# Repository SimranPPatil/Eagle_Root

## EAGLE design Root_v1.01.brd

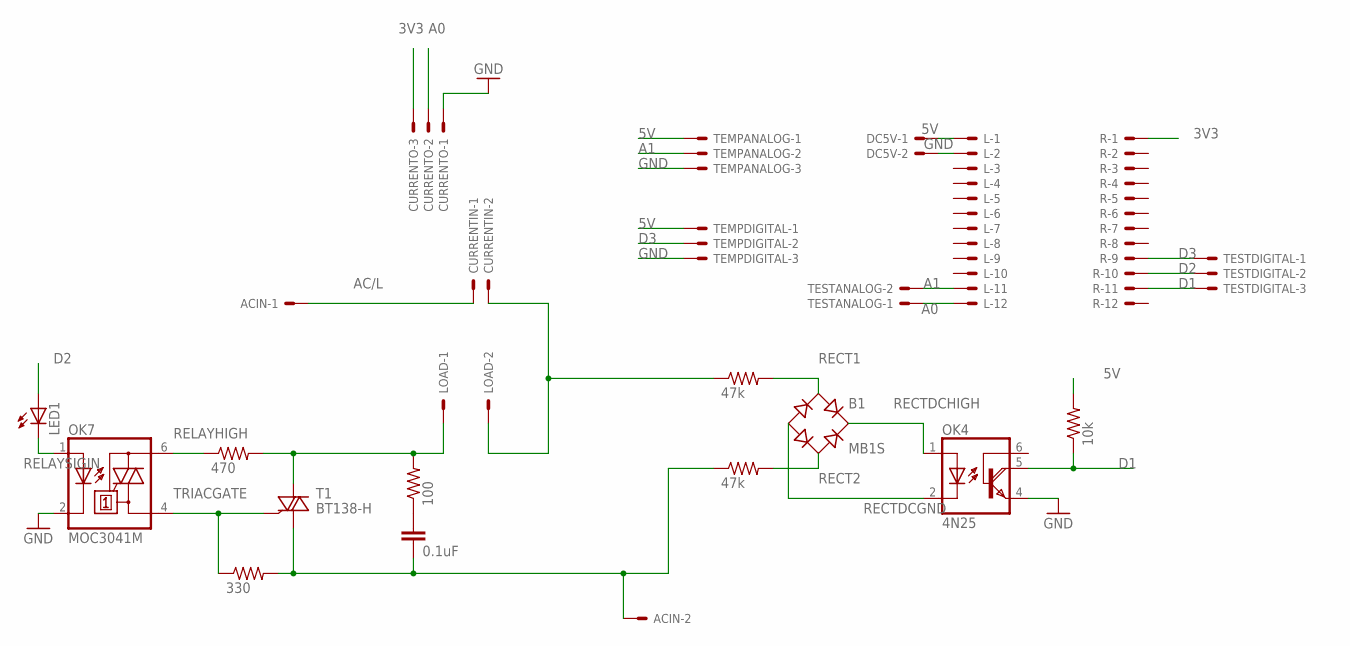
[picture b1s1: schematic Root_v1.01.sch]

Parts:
ACIN: 22-23-2021
B1: MB1S; SOIC-4
C4: 0.1uF; C5B3
CURRENTIN: 22-23-2021
CURRENTO: 22-23-2031
DC5V: 22-23-2021
L: 22-23-2121
LED1: N/A; LED_LD260
LOAD: 22-23-2021
OK4: 4N25; DIL06
OK7: MOC3041M; DIL06
R: 22-23-2121
R1, R3: 47k; 0204/7
R4: 330; 0204/7
R6: 100; 0204/7
R7: 470; 0204/7
R8: 10k; 0204/7
T1: BT138-H; TO220BH
TEMPANALOG: 22-23-2031
TEMPDIGITAL: 22-23-2031
TESTANALOG: 22-23-2021
TESTDIGITAL: 22-23-2031

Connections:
3V3: CURRENTO.3, R.1
5V: DC5V.1, L.1, R8.2, TEMPANALOG.1, TEMPDIGITAL.1
A0: CURRENTO.2, L.12, TESTANALOG.1
A1: L.11, TEMPANALOG.2, TESTANALOG.2
AC/L: ACIN.1, CURRENTIN.1
AC/N: ACIN.2, C4.2, R3.1, R4.2, T1.T1 (A1)
D1: OK4.5 (COL), R.11, R8.1, TESTDIGITAL.3
D2: LED1.A, R.10, TESTDIGITAL.2
D3: R.9, TEMPDIGITAL.2, TESTDIGITAL.1
GND: CURRENTO.1, DC5V.2, L.2, OK4.4 (E), OK7.2 (C), TEMPANALOG.3, TEMPDIGITAL.3
LOAD/L: CURRENTIN.2, LOAD.2, R1.1
LOAD/N: LOAD.1, R6.2, R7.2, T1.T2 (A2)
unnamed: C4.1, R6.1
RECT1: B1.~1 (AC1), R1.2
RECT2: B1.~2 (AC2), R3.2
RECTDCGND: B1.-, OK4.2 (C)
RECTDCHIGH: B1.+, OK4.1 (A)
RELAYHIGH: OK7.6 (A2), R7.1
RELAYSIGIN: LED1.K (C), OK7.1 (A)
TRIACGATE: OK7.4 (A1), R4.1, T1.G

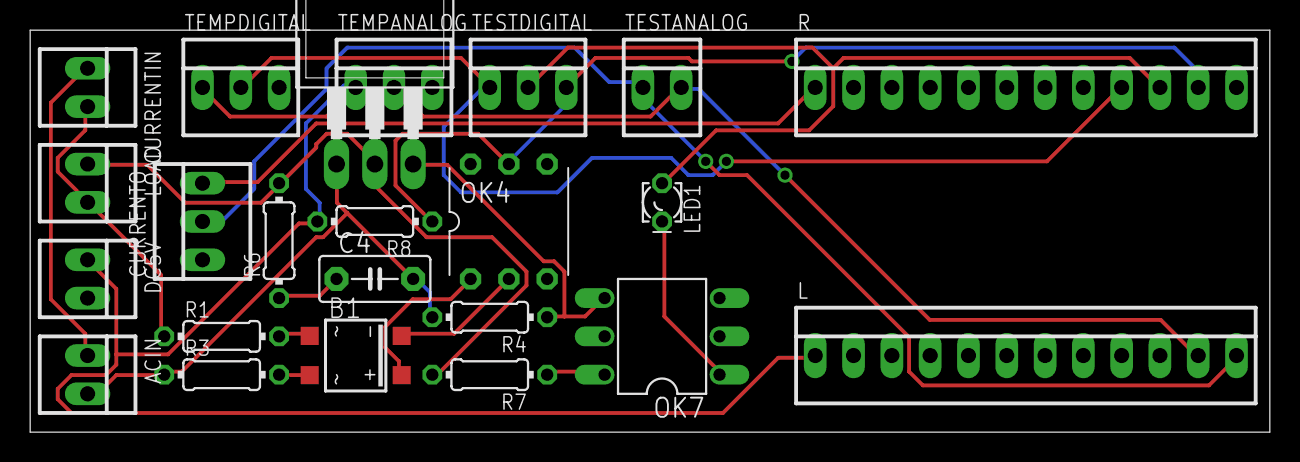
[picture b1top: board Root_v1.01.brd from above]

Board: 2 copper layers, 82.2 x 26.7 mm, 23 parts (0 on the bottom side), 20 nets.

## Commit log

2016-06-24 First Commit
    Downloaded Libraries and Schematics of first iteration, Going from P1
    to Photon and the root Circuitry
2016-06-24 p1 basic schematic
2016-06-24 Other Downloaded Libraries
2016-06-24 Replacement for power circuit
    IRM AC/DC
2016-06-29 additional stuff
